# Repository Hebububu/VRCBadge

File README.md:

<div align="center">

# VRCBadge

I made RFID namecard before (for friends and myself)<br>
and you know, all VRC players change avatar quite often.

After making those namecards 3 times (dumb),<br>
I decided to make a digital badge for myself. (simple + fun toy project!)

It's gonna be a wearable digital badge powered by ESP32-S3<br>
Namecard looking UI (Yes, changeable image ofc)<br>
editable profile information (twitter, discord etc..), and future RFID door key emulation.

This project is inspired by Github Conference Badge video, posted by Wes Bos. [Ref Video](https://youtu.be/_jPm_zN95FE?si=vHjaHDR8lpRF7iKP)

### Working Prototype

Badge UI running on a Guition JC8048W550 dev board (ESP32-S3 + 4.8" RGB parallel LCD with capacitive touch). Built with [Slint](https://slint.dev).

### Enclosure (WIP)

Enclosure drawn with Autodesk Fusion 360.

### Schematic (Future)

Custom 2-layer PCB designed for JLCPCB fabrication.
USB-C input with TP4056 LiPo charging, DW01A+FS8205A battery protection, and ME6211 3.3V LDO.
ESP32-S3-WROOM-1U drives a 3.5" SPI LCD with capacitive touch, while a MAX17048 fuel gauge tracks battery level over I2C.

</div>

## Documentation

See [/docs](./docs/README.md) for full documentation:

- [Hardware](./docs/hardware/) - ESP32-S3, custom PCB, display, BOM
- [Software](./docs/software/) - Architecture, API
- [RFID](./docs/rfid/) - Technical guide (future phase)

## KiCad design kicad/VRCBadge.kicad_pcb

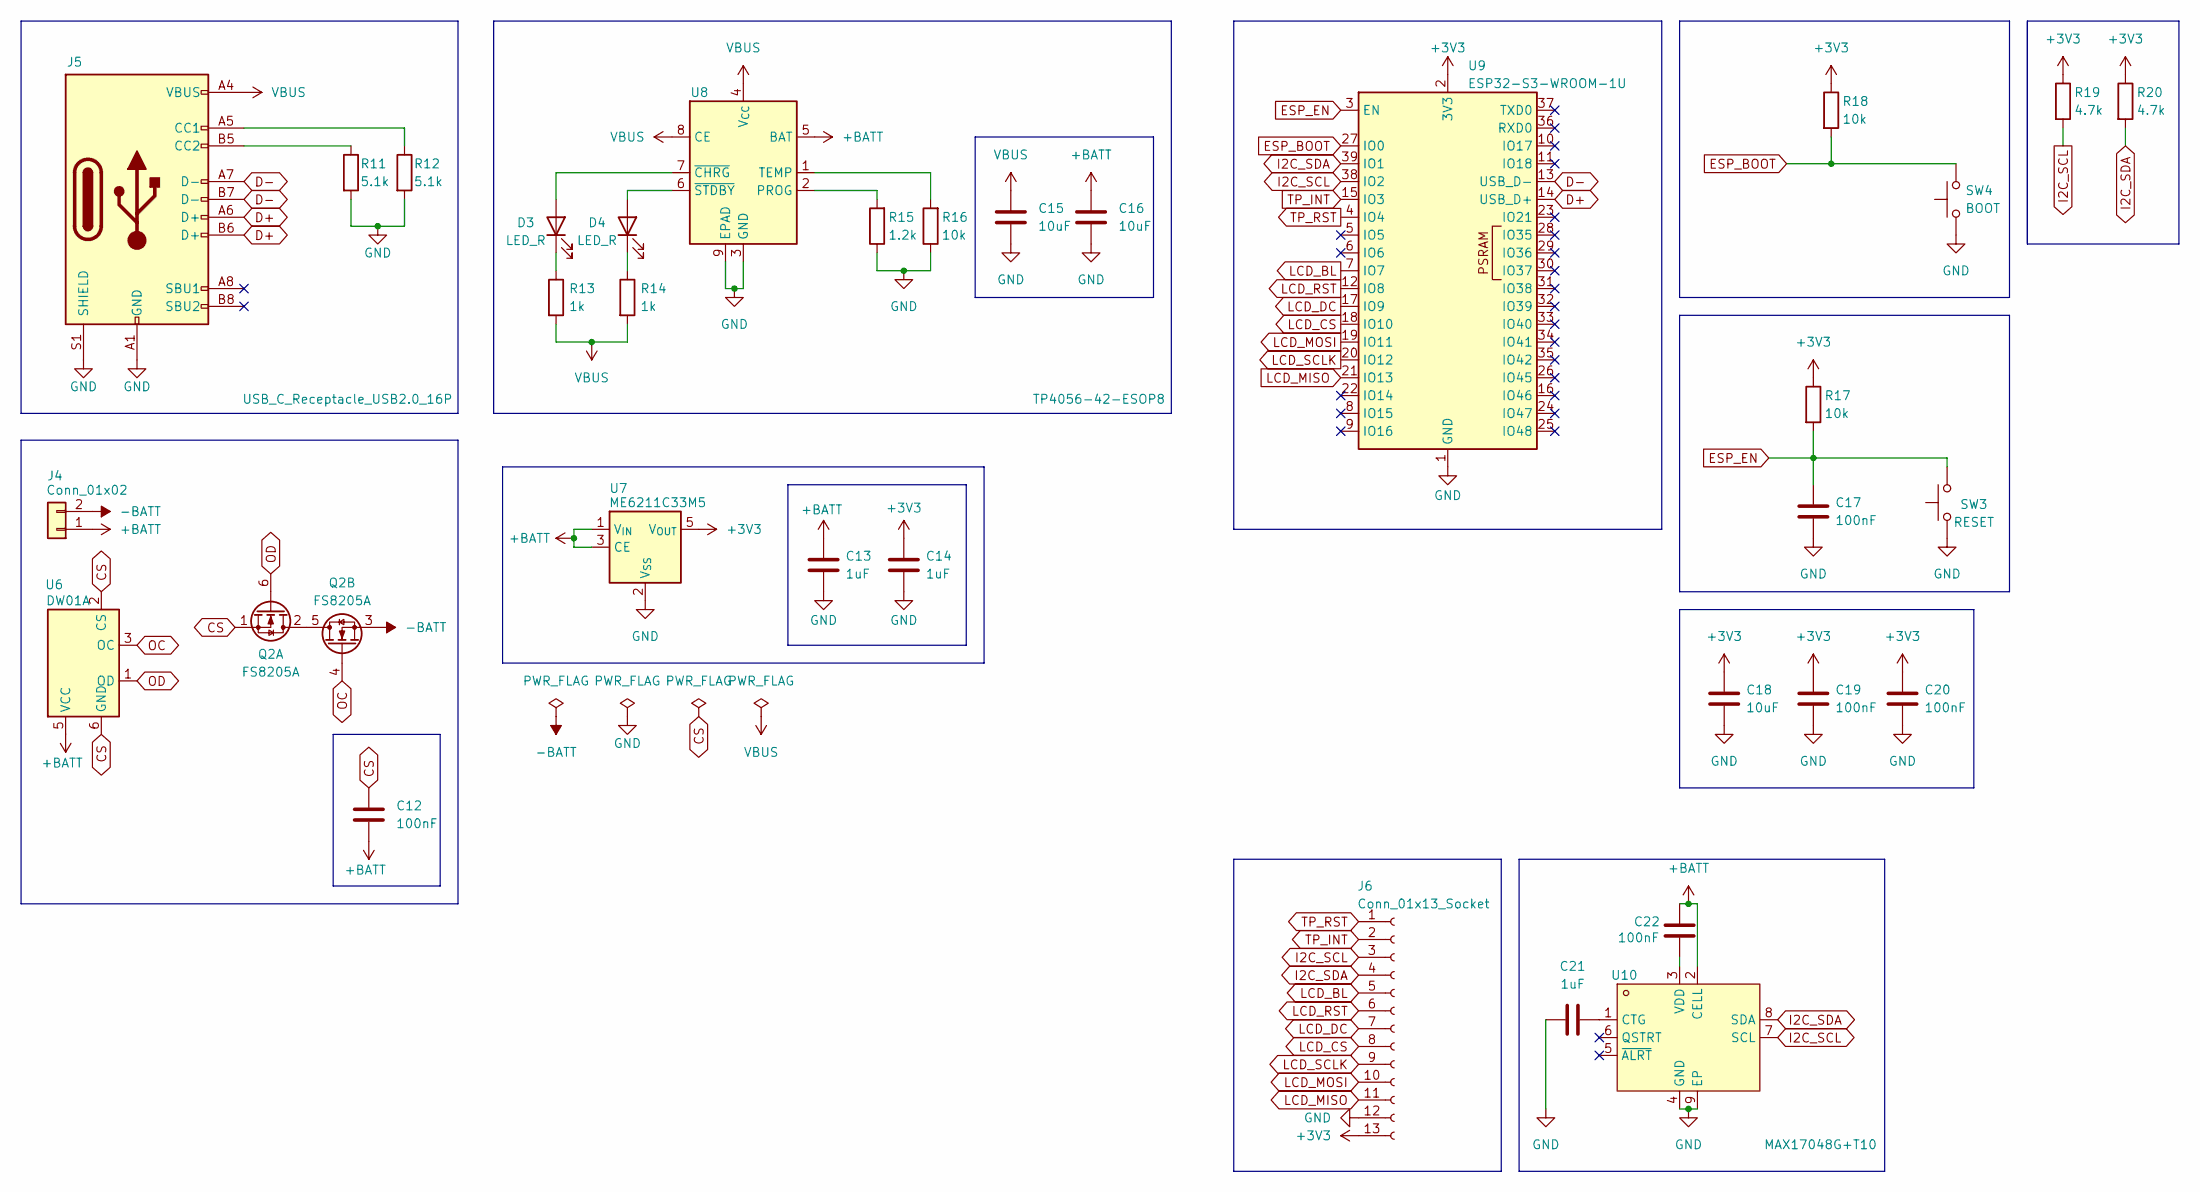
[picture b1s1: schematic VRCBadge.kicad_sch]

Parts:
C12, C17, C19, C20, C22: 100nF; C_0402_1005Metric
C13, C14, C21: 1uF; C_0402_1005Metric
C15, C16, C18: 10uF; C_0402_1005Metric
D3, D4: LED_R; LED_0402_1005Metric
J4: Conn_01x02; JST_PH_S2B-PH-K_1x02_P2.00mm_Horizontal
J5: USB_C_Receptacle_USB2.0_16P; USB_C_Receptacle_HRO_TYPE-C-31-M-12
J6: Conn_01x13_Socket; JST_GH_SM13B-GHS-TB_1x13-1MP_P1.25mm_Horizontal
Q2: FS8205A; SOT-23-6; LCSC Part C32254
R11, R12: 5.1k; R_0402_1005Metric
R13, R14: 1k; R_0402_1005Metric
R15: 1.2k; R_0402_1005Metric
R16, R17, R18: 10k; R_0402_1005Metric
R19, R20: 4.7k; R_0402_1005Metric
SW3: RESET; SW_SPST_TL3342
SW4: BOOT; SW_SPST_TL3342
U6: DW01A; SOT-23-6
U7: ME6211C33M5; SOT-23-5
U8: TP4056-42-ESOP8; SOIC-8-1EP_3.9x4.9mm_P1.27mm_EP2.41x3.3mm_ThermalVias
U9: ESP32-S3-WROOM-1U
U10: MAX17048G+T10; TDFN-8_L2.0-W2.0-P0.50-BL-EP1.2; LCSC Part C2682616

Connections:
+3V3: C14.1, C18.1, C19.1, C20.1, J6.13, R17.1, R18.1, R19.1, R20.1, U7.5 (V_{OUT}), U9.2 (3V3)
+BATT: C12.2, C13.1, C16.1, C22.1, J4.1, U6.5 (VCC), U7.1 (V_{IN}), U7.3 (CE), U8.5 (BAT), U10.2 (CELL)
-BATT: J4.2, Q2.3 (S)
CS: C12.1, Q2.1 (S), U6.2 (CS), U6.6 (GND)
D+: J5.A6 (D+), J5.B6 (D+), U9.14 (USB_D+)
D-: J5.A7 (D-), J5.B7 (D-), U9.13 (USB_D-)
ESP_BOOT: R18.2, SW4.2, U9.27 (IO0)
ESP_EN: C17.1, R17.2, SW3.1, U9.3 (EN)
GND: C13.2, C14.2, C15.2, C16.2, C17.2, C18.2, C19.2, C20.2, C21.2, J5.A1 (GND), J5.A12 (GND), J5.B1 (GND), J5.B12 (GND), J5.S1 (SHIELD), J6.12, R11.2, R12.2, R15.1, R16.1, SW3.2, SW4.1, U7.2 (V_{SS}), U8.3 (GND), U8.9 (EPAD), U9.1 (GND), U9.40 (GND), U9.41 (GND), U10.4 (GND), U10.9 (EP)
I2C_SCL: J6.3, R19.2, U9.38 (IO2), U10.7 (SCL)
I2C_SDA: J6.4, R20.2, U9.39 (IO1), U10.8 (SDA)
LCD_BL: J6.5, U9.7 (IO7)
LCD_CS: J6.8, U9.18 (IO10)
LCD_DC: J6.7, U9.17 (IO9)
LCD_MISO: J6.11, U9.21 (IO13)
LCD_MOSI: J6.10, U9.19 (IO11)
LCD_RST: J6.6, U9.12 (IO8)
LCD_SCLK: J6.9, U9.20 (IO12)
unnamed: D3.2 (A), U8.7 (~CHRG)
unnamed: D3.1 (K), R13.1
unnamed: D4.2 (A), U8.6 (~STDBY)
unnamed: D4.1 (K), R14.1
unnamed: J5.A5 (CC1), R12.1
unnamed: J5.B5 (CC2), R11.1
unnamed: Q2.2 (D), Q2.5 (D)
unnamed: R15.2, U8.2 (PROG)
unnamed: R16.2, U8.1 (TEMP)
unnamed: C21.1, U10.1 (CTG)
unnamed: C22.2, U10.3 (VDD)
OC: Q2.4 (G), U6.3 (OC)
OD: Q2.6 (G), U6.1 (OD)
TP_INT: J6.2, U9.15 (IO3)
TP_RST: J6.1, U9.4 (IO4)
VBUS: C15.1, J5.A4 (VBUS), J5.A9 (VBUS), J5.B4 (VBUS), J5.B9 (VBUS), R13.2, R14.2, U8.4 (V_{CC}), U8.8 (CE)

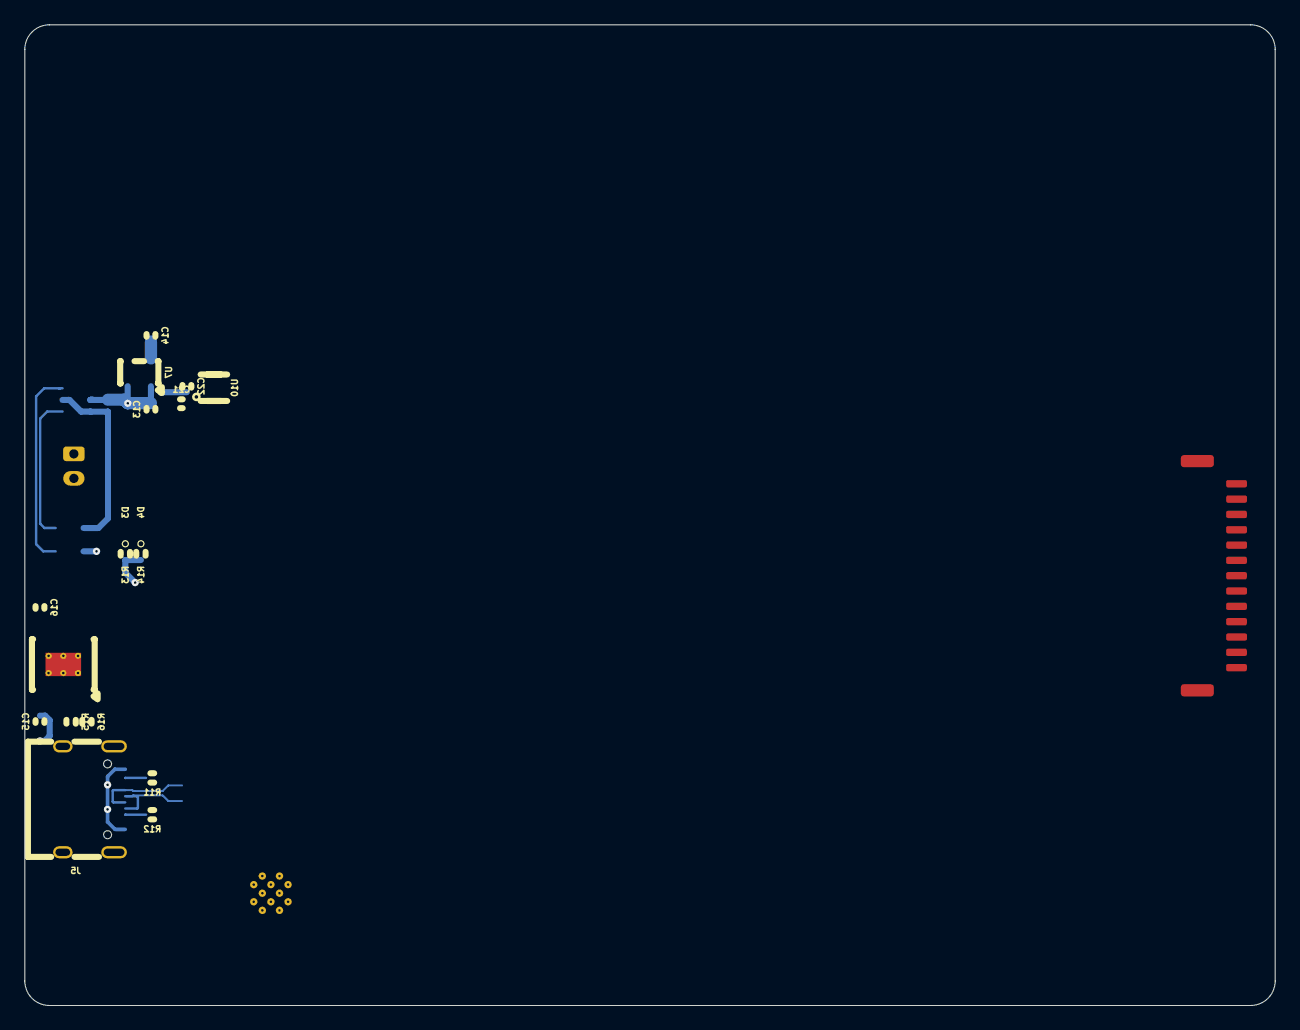
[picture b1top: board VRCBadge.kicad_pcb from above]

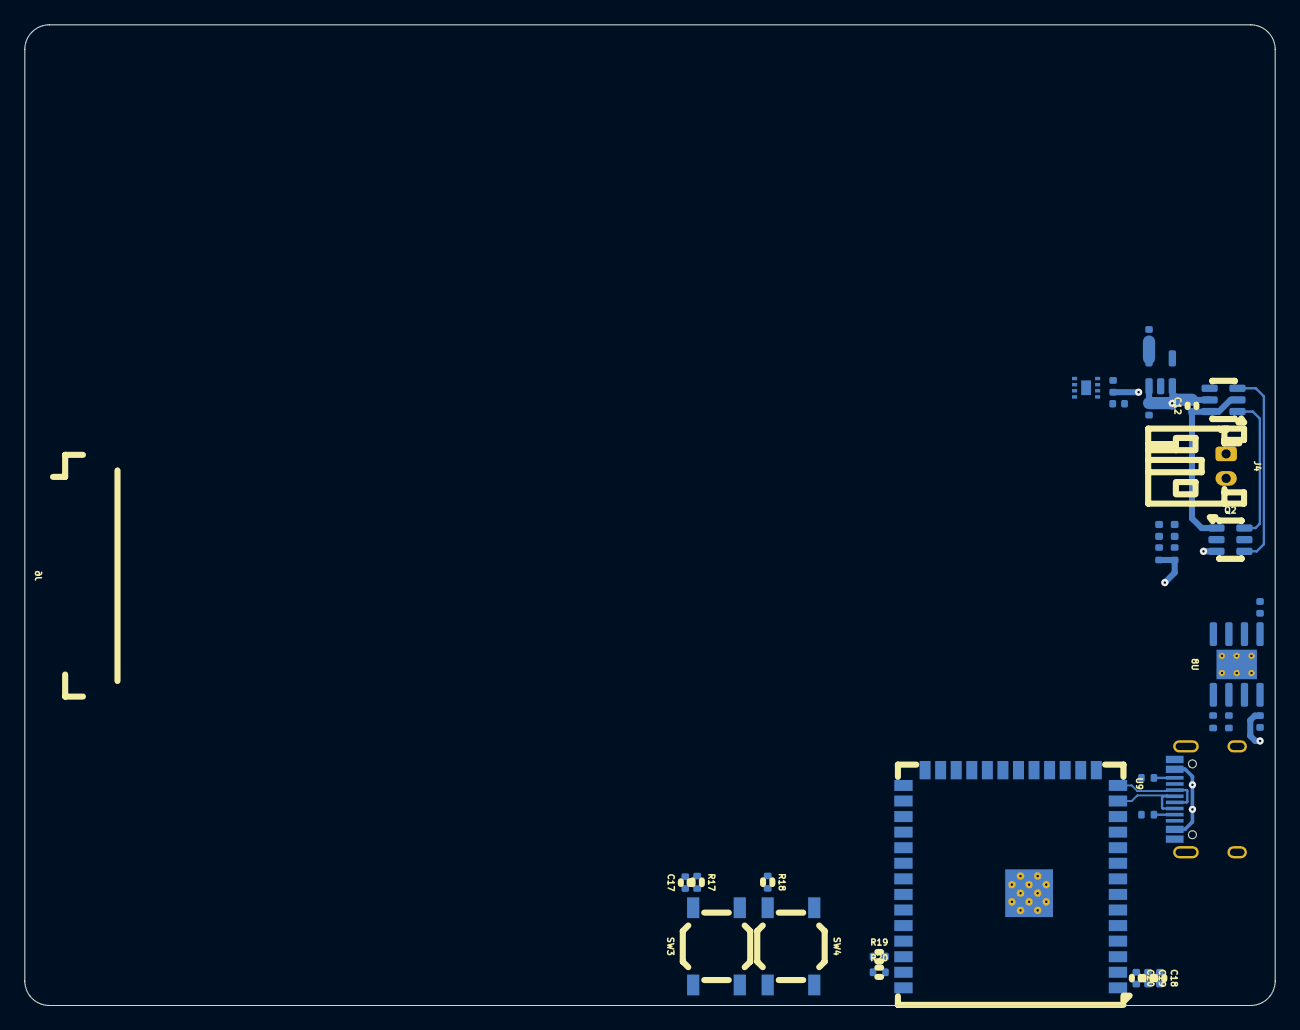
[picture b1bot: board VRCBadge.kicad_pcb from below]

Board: 4 copper layers, 102.0 x 80.0 mm, 34 parts (33 on the bottom side), 34 nets.

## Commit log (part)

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2026-01-27 docs: migrate hardware platform from CM4 to Pi Zero 2W with custom PCB
    Replace Raspberry Pi CM4 + carrier board + acrylic enclosure design
    with Pi Zero 2W + custom EasyEDA PCB + LiPo pouch cell. Updates all
    hardware docs, software architecture, and development roadmap to
    reflect the new platform. Adds PCB design guide with schematic blocks
    and fabrication notes.
2026-01-27 chore: update project configuration
2026-01-27 docs: add PCB design guideline and finalize component choices
    Add step-by-step PCB design walkthrough for EasyEDA Pro covering
    schematic blocks, layout, JLCPCB ordering, and hand-soldering.
    Finalize component selection: TPS61023 boost, MAX17048 fuel gauge,
    TPS22918 load switch with LCSC part numbers.
2026-01-28 docs: raspberryPi Z2W to esp32
2026-02-09 docs: remove Pi references, update to ESP32-S3 with Waveshare 3.5" RPi LCD (F)
2026-02-09 chore: update gitignore and remove obsolete root crate
2026-02-09 feat: add ESP32-S3 firmware scaffold with Slint UI
2026-02-09 feat: add badge assets with Phosphor battery icons
2026-02-09 docs: add Slint UI preview to README
2026-02-10 fix: enable custom partition table for SPIFFS storage layout
2026-02-10 fix: add rust-toolchain.toml and prevent usize underflow in display renderer
2026-02-10 fix: configure 16MB flash size and partition table path for esp-idf-sys build
2026-02-10 feat: add WiFi AP mode and HTTP server with health endpoint
2026-02-10 feat: add WiFi info page with live connected client count
2026-02-10 feat: add display brightness control with PWM backlight and settings slider
2026-02-10 feat: add background image upload via HTTP with browser-side resize
    Add web upload page at GET / that allows users to select an image,
    resize it to 480x320 in the browser, strip alpha to raw RGB888, and
    POST it to /api/background. The main loop polls for pending image
    data and updates the Slint UI background via SharedPixelBuffer.
    Note: requires PSRAM for the 450KB image buffer (ESP32-S3 only).
2026-02-10 feat: port firmware to ESP32-WROOM-32D (4MB flash)
    Target ESP32 (xtensa-esp32-espidf) with VSPI (SPI3) for display,
    remap all GPIOs to match ESP32-DevKitC V4 wiring, remove PSRAM
    config and background image feature (requires PSRAM).
    Replace all SVG assets with pre-rendered PNGs at display sizes and
    downscale profile image from 319x319 to 150x150 to reduce embedded
    resource data from 2.8MB to ~100KB. Enable SDF fonts and set
2026-02-10 fix: correct display color inversion and GT911 touch reset sequence
    Add ColorInversion::Inverted to ST7796S display builder to fix
    inverted colors on the Waveshare 3.5" panel.
    Fix GT911 touch by adding INT pin (GPIO26) to the reset sequence:
    drive INT low during reset to reliably select I2C address 0x5D,
    then keep it held low via mem::forget to prevent floating pin
    issues that caused I2C timeout errors after ~12 seconds.
2026-02-10 fix: correct display orientation and touch input handling
    Fix horizontal mirror by adding flip_vertical() to the ST7796S
    orientation (MADCTL MV-only instead of MV+MX).
    Fix GT911 touch: reconfigure INT pin (GPIO26) as input with pull-down
    after reset instead of holding as output (which prevented data-ready
    flag updates). Transform touch coordinates from portrait (320x480)
    to landscape (480x320) by swapping X/Y and inverting Y axis. Use last
2026-02-11 fix: debounce brightness slider to reduce display flicker
    Only update PWM duty when brightness changes by at least 2%,
    avoiding rapid LEDC reconfigurations during slider drag that
    caused visible backlight flicker.
2026-02-11 fix: backport display, touch, and build fixes from esp32-port
    - Display: add ColorInversion::Inverted and flip_vertical() for correct
    colors and non-mirrored output on Waveshare ST7796S panel
    - Touch: proper GT911 reset sequence with INT pin driven LOW for I2C
    address selection, then reconfigured as input with pull-down
    - Touch: coordinate transform from portrait GT911 to landscape display
    - Touch: track last_position for PointerReleased (fixes click detection)
2026-02-12 feat: add captive portal DNS server and detection endpoints
2026-02-13 feat: add captive portal with DNS server and dynamic AP IP
2026-02-13 feat: add captive portal, fix display/touch, and optimize SPI for ESP32-S3
2026-02-13 perf: full framebuffer rendering with DMA dirty-rect updates
2026-02-13 fix: switch from SDF to bitmap fonts to fix missing spaces in text
2026-02-13 feat: add logs page with ring buffer and about page with system info
2026-02-14 refactor: split http into web/ module with standalone SPA
2026-02-16 feat: add profile editing via web interface
2026-02-17 feat: add persistent storage and avatar upload
2026-02-18 feat: add color customization and optimize build for size
2026-02-23 docs: update architecture and API docs to match implementation
2026-02-25 docs: AN11756
2026-02-26 docs: WaveShare 3.5 Spi LCD (F)
2026-02-26 feat: KiCad project init
2026-02-26 feat: mcu schematic
2026-02-27 chore: add KiCad-specific entries to .gitignore
2026-02-27 feat: add power, peripheral schematics and custom component libraries
2026-02-27 docs: PCB layout board specification and component placement
2026-02-27 docs: add schematic image and hardware description to README
2026-02-28 docs: update hardware overview to match current schematic
2026-03-01 docs: add PCB layout link to index and clarify unused MISO pin
2026-03-02 fix: rewire MAX17048 CELL pin from +3V3 to +BATT
2026-03-02 feat: assign footprints and add no_connect flags for PCB readiness
    - Assign footprints to 28 root-sheet components (0603 passives,
    0805 for 10uF, TL3342 switches, HRO USB-C, JST-PH/GH connectors)
    - Add no_connect flags to MAX17048 ALRT and QSTRT pins
    - Rewire MAX17048 CELL pin from +3V3 to +BATT on root sheet
2026-03-02 refactor: flatten schematic to single root sheet and fix ERC violations
    - Remove hierarchical sub-sheets (power, mcu, peripheral) that
    duplicated root-sheet components and caused ERC conflicts
    - Fix MAX17048 symbol pin types from unspecified to correct
    electrical types (power_in, bidirectional, input, passive, etc.)
    - Sync DW01A lib_symbol with KiCad Battery_Management library
2026-03-02 docs: add display module mechanical dimensions from specsheet
    Extract measurements from Waveshare 3.5" RPi LCD (F) specsheet:
    panel 92.44x61.00mm, active area 73.84x49.36mm, stack height
    14.60mm, back PCB 56.00mm wide. Update component references to
    match flattened root sheet.
2026-03-02 feat: import netlist into PCB layout
2026-03-02 feat: add board outline and initial component placement
2026-03-03 chore: change usb data line global label and update footprint to 0402_1005
2026-03-03 feat: add design rule for jlcpcb
2026-03-03 chore: change project settings - diff pair setup - silk text setup - via dimention setup - layer pair setup - route clearance setup - netclass setup
2026-03-04 chore: add track width rules
2026-03-05 wip: pcb
2026-03-06 feat: fusion 360 init
2026-03-07 feat: update enclosure drawing
2026-03-07 feat: temp screen model
2026-03-07 feat: assembly init
2026-03-07 chore: enclosure images
2026-03-07 docs: update enclosure images
2026-03-12 feat: port firmware to JC8048W550C dev board (800x480 RGB parallel display)
    Replace SPI/mipidsi display driver with ESP-IDF RGB parallel panel via raw FFI
    for the ST7262-based JC8048W550C board. Key changes:
    - display.rs: DMA-driven RGB565 framebuffer in PSRAM with bounce buffers
    - main.rs: GPIO 2 backlight (600Hz PWM), new touch pins (19/20/38)
    - touch.rs: simplified GT911 polling, direct coordinate mapping
    - badge.slint: redesigned UI for 800x480 with PageHeader component
2026-03-12 feat: add rounded corners to avatar image via Rust-side pixel processing
    Slint's software renderer does not support border-radius clipping
    (upstream #4176). Work around this by painting corner pixels outside
    the rounded rect with the container background color in Rust before
    passing the image to Slint.
    - Add apply_rounded_corners() helper with circle-based corner test
    - Apply rounding on both SPIFFS load and HTTP upload paths
2026-03-12 chore: remove touch debug logging
2026-03-12 feat: add virtual keyboard and WiFi icon assets
    Add on-screen QWERTY keyboard for touchscreen text input (WiFi
    password entry). Simplified from the official Slint virtual_keyboard
    example using Unicode glyphs for special keys instead of SVG assets.
    - New ui/virtual_keyboard.slint with letters + numbers/symbols layouts
    - Keyboard overlays bottom 192px, visibility bound to TextInputInterface
    - Key dispatch wired in main.rs via VirtualKeyboardHandler callback
2026-03-12 feat: add WiFi station mode backend and badge WiFi indicator
    Rewrite wifi.rs to support AP+STA mixed mode via Configuration::Mixed.
    Add scan(), connect_sta(), disconnect_sta(), sta_status() functions.
    On connect failure, automatically revert to AP-only mode.
    - storage.rs: add NVS save/load/delete for WiFi credentials (SSID+password)
    - main.rs: auto-connect to saved network on boot (10s timeout),
    poll STA status every ~2s, shared wifi handle via Arc<Mutex<>>
2026-03-12 feat: add WiFi connect page UI, toast notifications, and wire all callbacks
    Complete Stage 3 of WiFi station mode implementation:
    - WiFi connect page (page 5): scan for networks, select AP, enter
    password, connect/disconnect/forget buttons
    - WiFi page expanded with AP section, Station section showing
    connection status, and 'Connect to Network' navigation
    - Toast notification overlay with 5-second auto-hide for boot
2026-03-15 fix: WiFi scan requires STA interface, temporarily switch to mixed mode
    WiFi scan was hanging because esp_wifi_scan_start requires the STA
    interface to be active. In AP-only mode, the scan blocks indefinitely
    since no STA interface exists.
    Fix: detect AP-only configuration before scanning, temporarily switch
    to Mixed mode (AP+STA with dummy STA config), perform the scan, then
    revert to AP-only. If already in Mixed mode (STA connected), scan
2026-03-15 perf: increase pixel clock to 21MHz, reduce poll interval, increase stack
    - Pixel clock 16MHz -> 21MHz (~39 -> ~51 FPS panel refresh rate)
    - Main loop sleep cap 16ms -> 8ms (faster touch response and rendering)
    - Main task stack 32KB -> 64KB (required for WiFi UI + Slint rendering)
    - Remove unused flush_dirty_region() (no-op since bounce buffers
    handle cache coherency; render result is no longer captured)
2026-03-15 docs: add OTA firmware update design document
    Two-stage plan for OTA updates via GitHub releases:
    - Stage 1: partition table redesign (factory -> ota_0/ota_1) + ota.rs module
    - Stage 2: About page UI + auto-check on STA connect
    Includes architecture flowchart, sequence diagram, and partition
    layout diagrams in Mermaid.
2026-03-22 fix: improve WiFi connect page UX and move operations to background
    UI layout fixes:
    - Hide scan results list when virtual keyboard is open so password
    field and action buttons remain visible above the keyboard
    - Add overflow: elide to status text, STA info, and selected SSID
    to prevent long strings from breaking the layout
    - Add empty state text when scan results are empty
